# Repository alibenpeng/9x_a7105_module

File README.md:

## JR/Graupner/FlySky/Turnigy compatible A7105 TX module

This module replaces the carrier board of the stock module found in FlySky/Turnigy 9x transmitters (and probably others).
It is possible to re-use almost all components from the original carrier board (bind-button, connector, regulator and caps).
To use the original A7105 TX module, you'll have to cut open the metal casing (if applicable) and remove the MCU.

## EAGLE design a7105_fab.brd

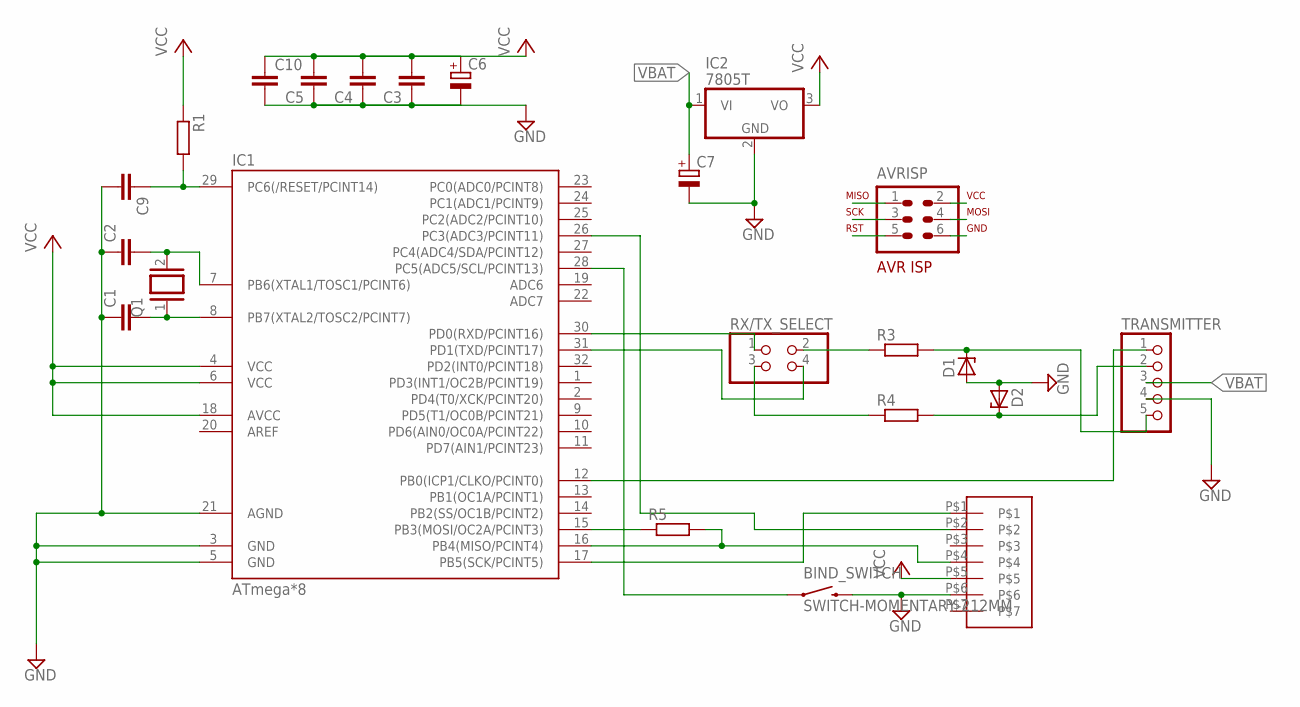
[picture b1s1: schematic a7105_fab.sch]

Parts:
AVRISP: AVR-ISP-6VERT; AVR-ISP-6
BIND_SWITCH: SWITCH-MOMENTARY-212MM; TACTILE-PTH-12MM
C1, C2, C3, C4, C5, C9, C10: C-EUC0805; C0805
C6, C7: CPOL-EUE2.5-6; E2,5-6
D1, D2: ZENER-DIODESOD80C; SOD80C
IC1: ATmega*8; TQFP32-08
IC2: 7805T; TO220H
Q1: XTAL/S; QS
R1, R3, R4, R5: R-EU_M0805; M0805
RX/TX_SELECT: PINHD-2X2; 2X02
TRANSMITTER: PINHD-1X5; 1X05
U$1: PIN-HEAD7-1.8

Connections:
AVR_RXD: IC1.30 (PD0(RXD/PCINT16)), RX/TX_SELECT.1
AVR_TXD: IC1.31 (PD1(TXD/PCINT17)), RX/TX_SELECT.4
CE: IC1.26 (PC3(ADC3/PCINT11)), U$1.P$2
GND: AVRISP.6, BIND_SWITCH.3 (2), C1.1, C2.1, C3.1, C4.1, C5.1, C6.-, C7.-, C9.2, C10.2, D1.A, D2.A, IC1.3 (GND), IC1.5 (GND), IC1.21 (AGND), TRANSMITTER.4, U$1.P$6
MISO: AVRISP.1, IC1.16 (PB4(MISO/PCINT4)), R5.2, U$1.P$4
MOSI: AVRISP.4, IC1.15 (PB3(MOSI/OC2A/PCINT3)), R5.1
unnamed: D2.C, R4.2, TRANSMITTER.2
unnamed: R4.1, RX/TX_SELECT.3
unnamed: R3.1, RX/TX_SELECT.2
unnamed: D1.C, R3.2, TRANSMITTER.5
unnamed: C1.2, IC1.8 (PB7(XTAL2/TOSC2/PCINT7)), Q1.1
unnamed: C2.2, IC1.7 (PB6(XTAL1/TOSC1/PCINT6)), Q1.2
unnamed: BIND_SWITCH.1, IC1.28 (PC5(ADC5/SCL/PCINT13))
PPM: IC1.12 (PB0(ICP1/CLKO/PCINT0)), TRANSMITTER.1
RST: AVRISP.5, C9.1, IC1.29 (PC6(/RESET/PCINT14)), R1.2
SCK: AVRISP.3, IC1.17 (PB5(SCK/PCINT5)), U$1.P$1
VBAT: C7.+, IC2.1 (VI), TRANSMITTER.3
VCC: AVRISP.2, C3.2, C4.2, C5.2, C6.+, C10.1, IC1.4 (VCC), IC1.6 (VCC), IC1.18 (AVCC), IC2.3 (VO), R1.1, U$1.P$5

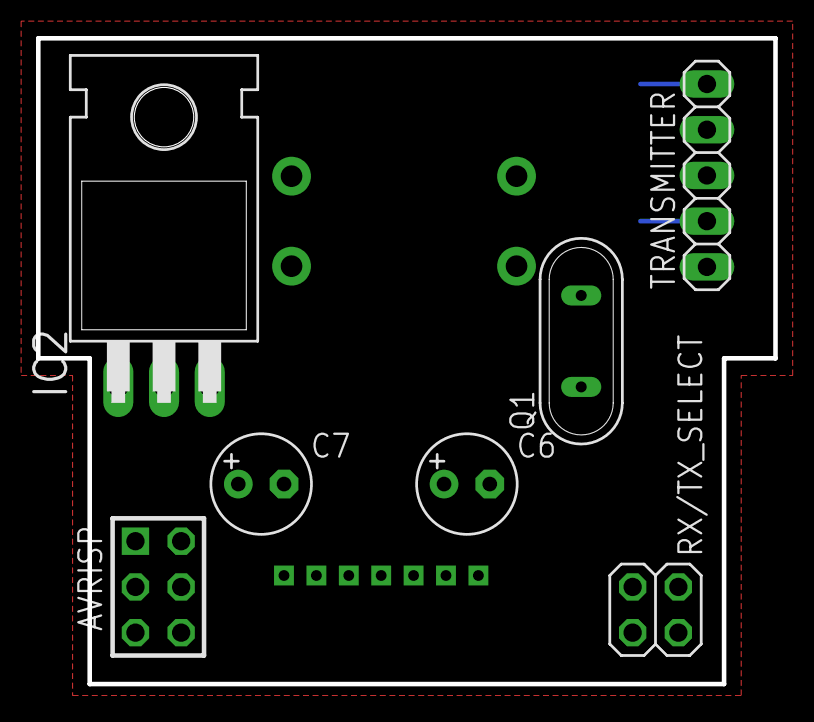
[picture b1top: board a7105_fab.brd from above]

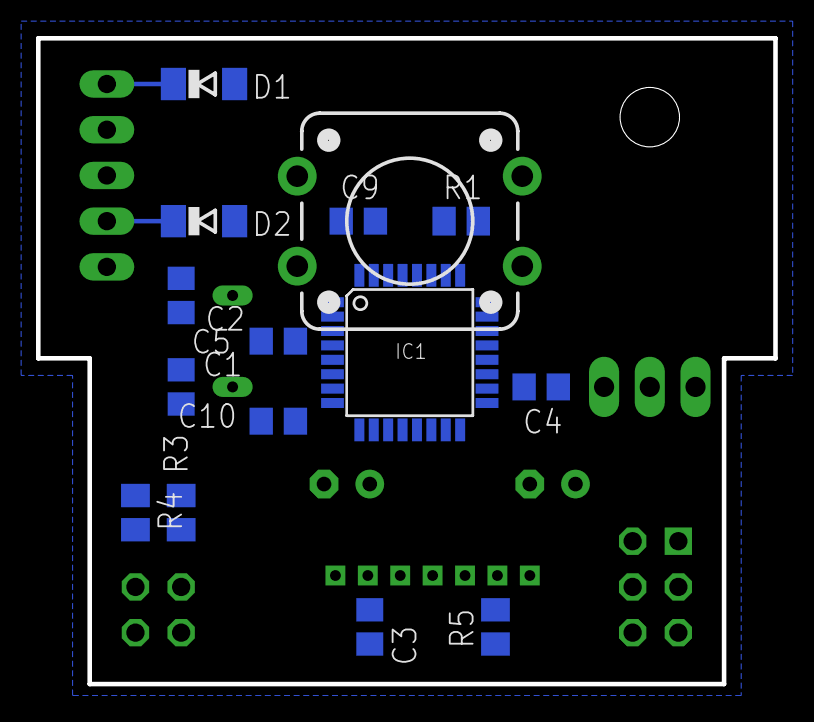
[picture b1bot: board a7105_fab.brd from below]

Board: 2 copper layers, 41.0 x 35.9 mm, 23 parts (16 on the bottom side), 18 nets.

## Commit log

2014-06-30 added readme

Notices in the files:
parts and their libraries:
SparkFun-Electromechanical: Licensing: CC v3.0 Share-Alike You are welcome to use this library for commercial purposes.
